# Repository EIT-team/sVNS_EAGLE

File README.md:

# sVNS_15chan_EAGLE

EAGLE project, schematic and layout files of the 15-channel selective Vagus Nerve stimulator. Eagle-based 4-layer PCB with SMD assembly were produced using PCBway services.

Note: 15 channels in the files names refer to a number of the output demultiplexer states.

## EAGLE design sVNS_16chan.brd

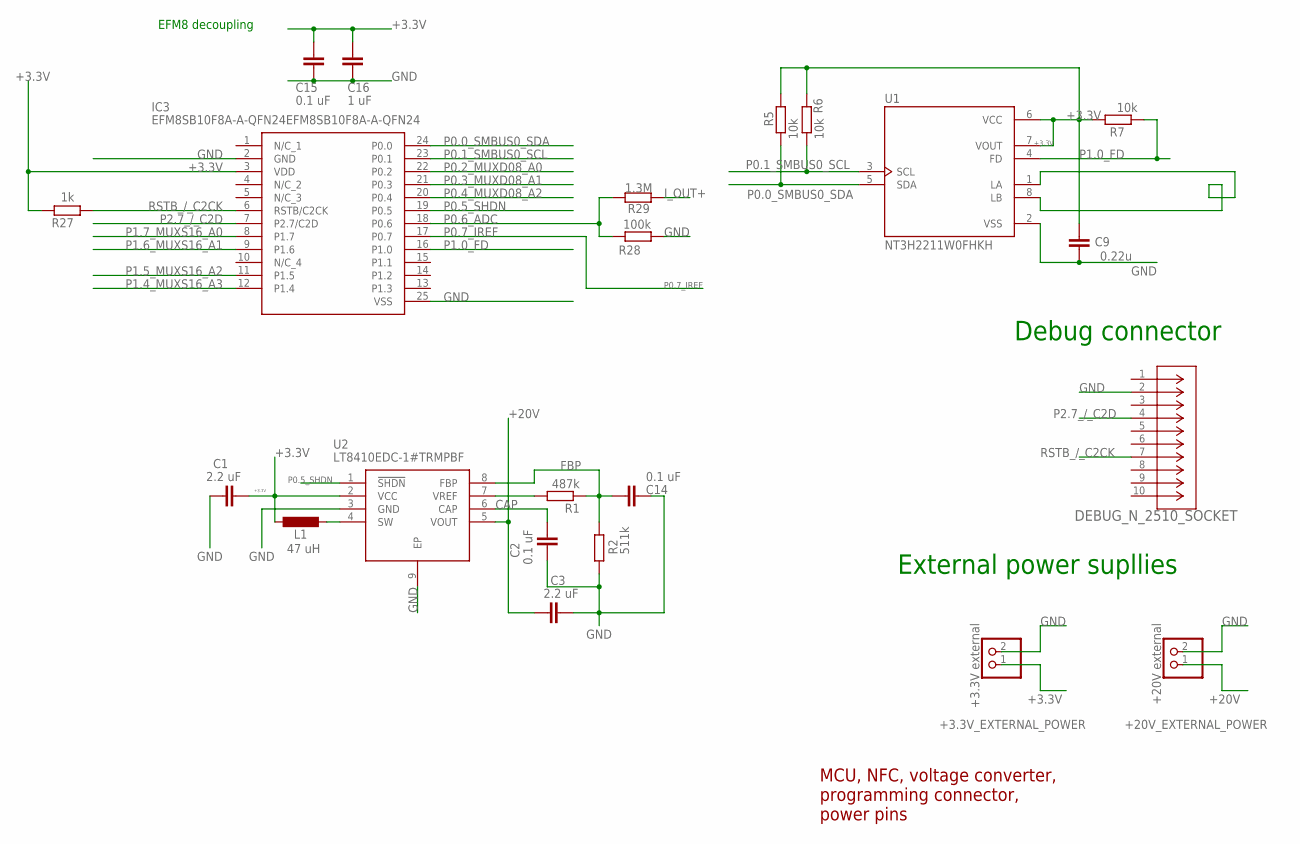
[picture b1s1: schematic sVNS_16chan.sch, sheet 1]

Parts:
+3.3V_EXTERNAL_POWER: +3.3V external; 1X02
+20V_EXTERNAL_POWER: +20V external; 1X02
C1, C3: 2.2 uF; C0603
C2, C14, C15: 0.1 uF; C0603
C9: 0.22u; C0603
C16: 1 uF; C0603
DEBUG_N_2510_SOCKET: N2510-6002RB; CONN_6002RB_3MM
IC3: EFM8SB10F8A-A-QFN24EFM8SB10F8A-A-QFN24; QFN50P400X400X80-25T245N
L1: 47 uH; 0603PS-473KRC
R1: 487k; R0603
R2: 511k; R0603
R5, R6, R7: 10k; R0603
R27: 1k; R0603
R28: 100k; R0603
R29: 1.3M; R0603
U1: NT3H2211W0FHKH; IC_NT3H2211W0FHKH
U2: LT8410EDC-1#TRMPBF; SON45P200X200X80-9N

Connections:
+3.3V: +3.3V_EXTERNAL_POWER.1, C1.2, C9.1, C15.2, C16.1, IC3.3 (VDD), L1.P$1 (1), R5.2, R6.2, R7.2, R27.2, U1.6 (VCC), U1.7 (VOUT), U2.2 (VCC); also elsewhere on the board
+20V: +20V_EXTERNAL_POWER.1, C3.1, U2.5 (VOUT); also elsewhere on the board
CAP: C2.2, U2.6 (CAP)
FBP: C14.2, R1.1, R2.2, U2.8 (FBP)
GND: +3.3V_EXTERNAL_POWER.2, +20V_EXTERNAL_POWER.2, C1.1, C2.1, C3.2, C9.2, C14.1, C15.1, C16.2, DEBUG_N_2510_SOCKET.2, IC3.2 (GND), IC3.25 (VSS), R2.1, R28.2, U1.2 (VSS), U2.3 (GND), U2.9 (EP); also elsewhere on the board
I_OUT+: R29.1; also elsewhere on the board
LA: U1.1 (LA), U1.8 (LB)
P0.0_SMBUS0_SDA: IC3.24 (P0.0), R5.1, U1.5 (SDA)
P0.1_SMBUS0_SCL: IC3.23 (P0.1), R6.1, U1.3 (SCL)
P0.2_MUXD08_A0: IC3.22 (P0.2); also elsewhere on the board
P0.3_MUXD08_A1: IC3.21 (P0.3); also elsewhere on the board
P0.4_MUXD08_A2: IC3.20 (P0.4); also elsewhere on the board
P0.5_SHDN: IC3.19 (P0.5), U2.1 (!SHDN); also elsewhere on the board
P0.6_ADC: IC3.18 (P0.6), R28.1, R29.2
P0.7_IREF: IC3.17 (P0.7); also elsewhere on the board
P1.0_FD: IC3.16 (P1.0), R7.1, U1.4 (FD)
P1.4_MUXS16_A3: IC3.12 (P1.4); also elsewhere on the board
P1.5_MUXS16_A2: IC3.11 (P1.5); also elsewhere on the board
P1.6_MUXS16_A1: IC3.9 (P1.6); also elsewhere on the board
P1.7_MUXS16_A0: IC3.8 (P1.7); also elsewhere on the board
P2.7_/_C2D: DEBUG_N_2510_SOCKET.4, IC3.7 (P2.7/C2D)
RSTB_/_C2CK: DEBUG_N_2510_SOCKET.7, IC3.6 (RSTB/C2CK), R27.1
SW: L1.P$2 (2), U2.4 (SW)
VREF: R1.2, U2.7 (VREF)

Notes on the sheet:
External power supllies
Debug connector
EFM8 decoupling
MCU, NFC, voltage converter, programming connector, power pins

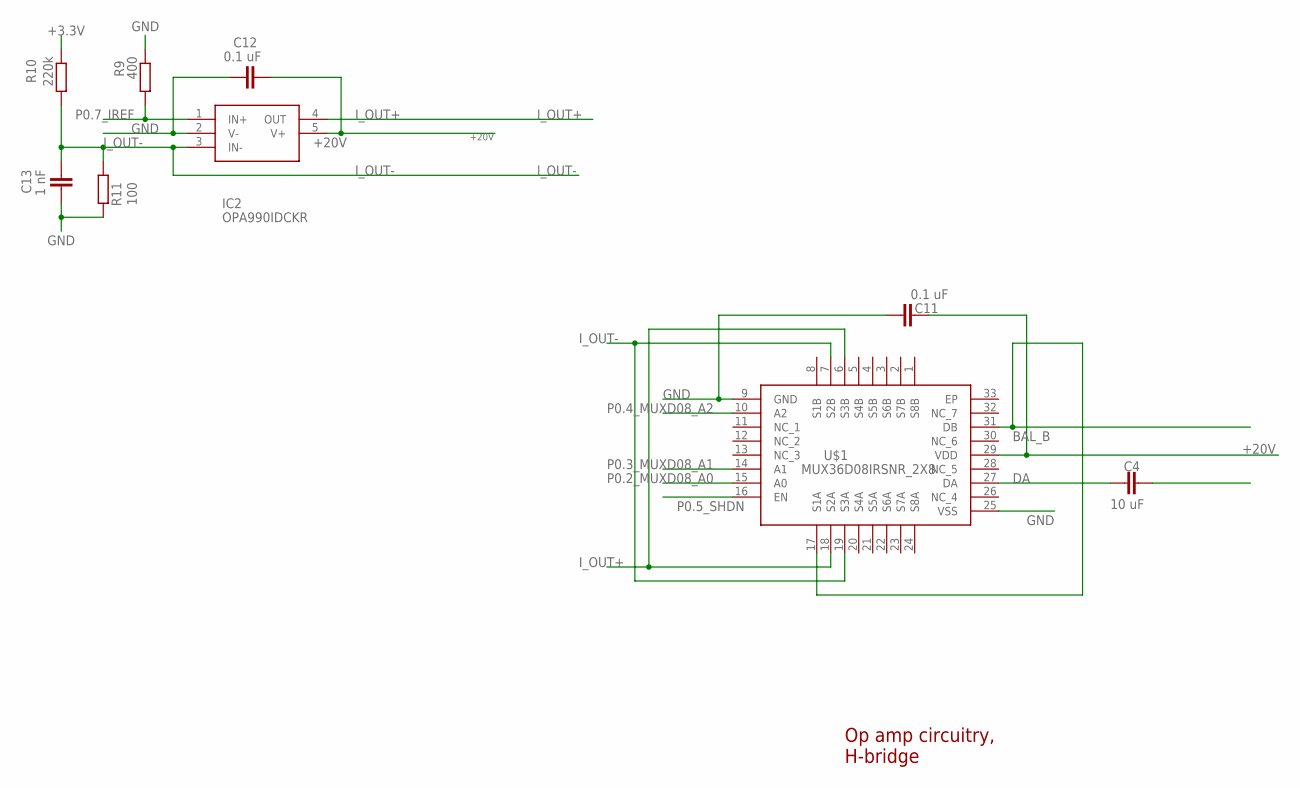
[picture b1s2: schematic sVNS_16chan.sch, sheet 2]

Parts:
C4: 10 uF; C0603
C11, C12: 0.1 uF; C0603
C13: 1 nF; C0603
IC2: OPA990IDCKR; SOT65P210X110-5N
R9: 400; R0603
R10: 220k; R0603
R11: 100; R0603
U$1: MUX36D08IRSNR_2X8; QFN40P400X400X80-33N_2X8

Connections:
+3.3V: R10.1; also elsewhere on the board
+20V: C11.2, C12.1, IC2.5 (V+), U$1.29 (VDD); also elsewhere on the board
BAL_A: C4.2; also elsewhere on the board
BAL_B: U$1.17 (S1A), U$1.31 (DB); also elsewhere on the board
DA: C4.1, U$1.27 (DA)
GND: C11.1, C12.2, C13.1, IC2.2 (V-), R9.1, R11.2, U$1.9 (GND), U$1.25 (VSS); also elsewhere on the board
I_OUT+: IC2.4 (OUT), U$1.6 (S3B), U$1.18 (S2A); also elsewhere on the board
I_OUT-: C13.2, IC2.3 (IN-), R10.2, R11.1, U$1.7 (S2B), U$1.19 (S3A)
P0.2_MUXD08_A0: U$1.15 (A0); also elsewhere on the board
P0.3_MUXD08_A1: U$1.14 (A1); also elsewhere on the board
P0.4_MUXD08_A2: U$1.10 (A2); also elsewhere on the board
P0.5_SHDN: U$1.16 (EN); also elsewhere on the board
P0.7_IREF: IC2.1 (IN+), R9.2; also elsewhere on the board

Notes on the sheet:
Op amp circuitry, H-bridge

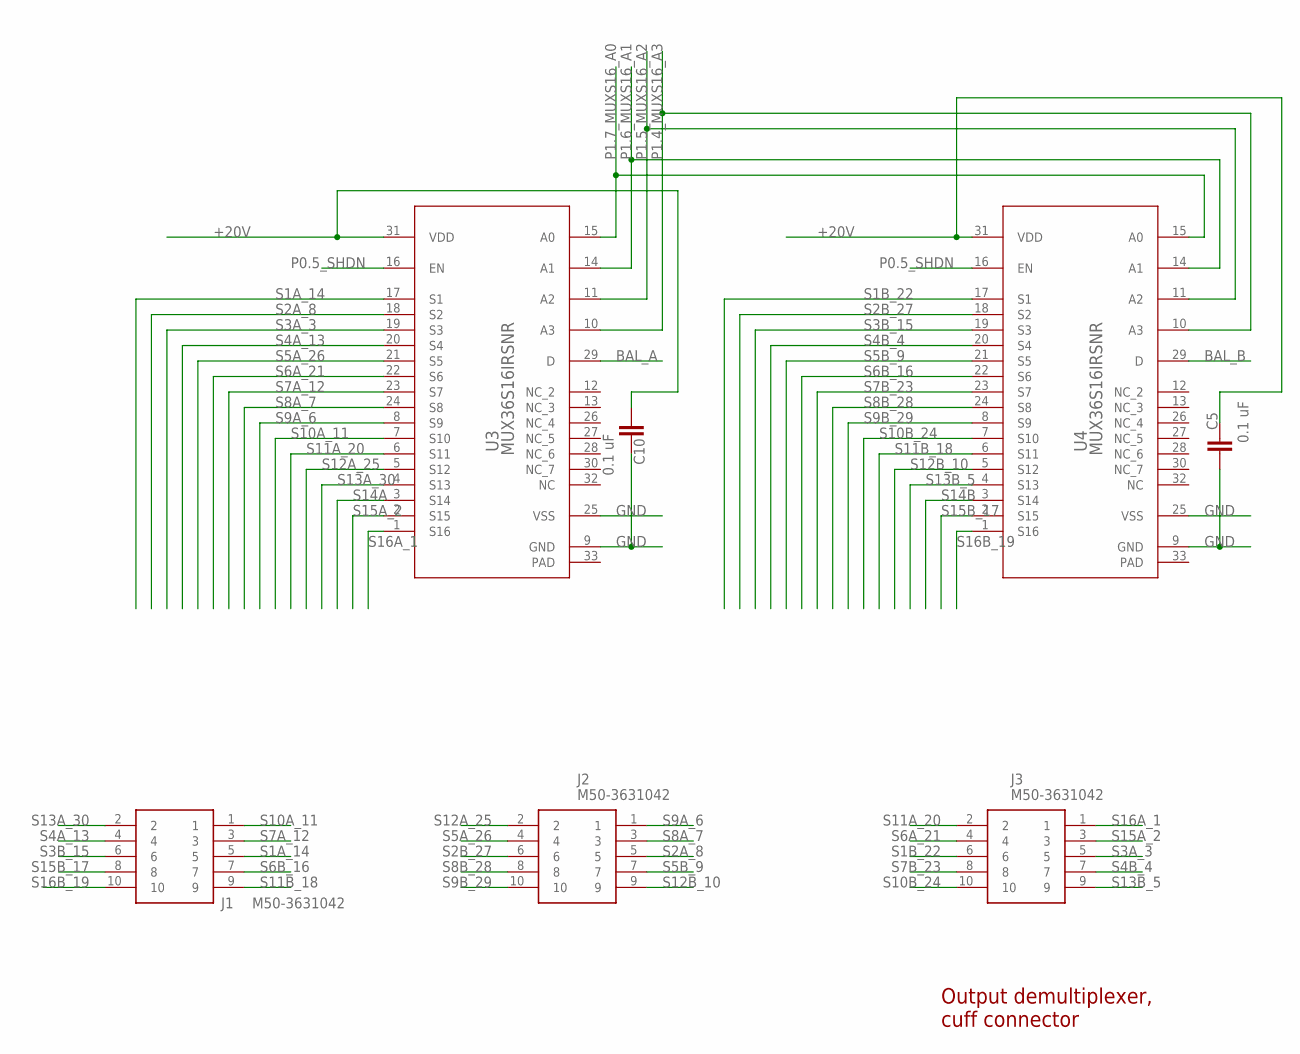
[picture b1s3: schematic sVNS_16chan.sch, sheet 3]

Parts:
C5, C10: 0.1 uF; C0603
J1, J2, J3: M50-3631042; M503631042
U3, U4: MUX36S16IRSNR; RSN0032B

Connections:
+20V: C5.2, C10.1, U3.31 (VDD), U4.31 (VDD); also elsewhere on the board
BAL_A: U3.29 (D); also elsewhere on the board
BAL_B: U4.29 (D); also elsewhere on the board
GND: C5.1, C10.2, U3.9 (GND), U3.25 (VSS), U4.9 (GND), U4.25 (VSS); also elsewhere on the board
P0.5_SHDN: U3.16 (EN), U4.16 (EN); also elsewhere on the board
P1.4_MUXS16_A3: U3.10 (A3), U4.10 (A3); also elsewhere on the board
P1.5_MUXS16_A2: U3.11 (A2), U4.11 (A2); also elsewhere on the board
P1.6_MUXS16_A1: U3.14 (A1), U4.14 (A1); also elsewhere on the board
P1.7_MUXS16_A0: U3.15 (A0), U4.15 (A0); also elsewhere on the board
S1A_14: J1.5, U3.17 (S1)
S1B_22: J3.6, U4.17 (S1)
S2A_8: J2.5, U3.18 (S2)
S2B_27: J2.6, U4.18 (S2)
S3A_3: J3.5, U3.19 (S3)
S3B_15: J1.6, U4.19 (S3)
S4A_13: J1.4, U3.20 (S4)
S4B_4: J3.7, U4.20 (S4)
S5A_26: J2.4, U3.21 (S5)
S5B_9: J2.7, U4.21 (S5)
S6A_21: J3.4, U3.22 (S6)
S6B_16: J1.7, U4.22 (S6)
S7A_12: J1.3, U3.23 (S7)
S7B_23: J3.8, U4.23 (S7)
S8A_7: J2.3, U3.24 (S8)
S8B_28: J2.8, U4.24 (S8)
S9A_6: J2.1, U3.8 (S9)
S9B_29: J2.10, U4.8 (S9)
S10A_11: J1.1, U3.7 (S10)
S10B_24: J3.10, U4.7 (S10)
S11A_20: J3.2, U3.6 (S11)
S11B_18: J1.9, U4.6 (S11)
S12A_25: J2.2, U3.5 (S12)
S12B_10: J2.9, U4.5 (S12)
S13A_30: J1.2, U3.4 (S13)
S13B_5: J3.9, U4.4 (S13)
S14A: U3.3 (S14)
S14B: U4.3 (S14)
S15A_2: J3.3, U3.2 (S15)
S15B_17: J1.8, U4.2 (S15)
S16A_1: J3.1, U3.1 (S16)
S16B_19: J1.10, U4.1 (S16)

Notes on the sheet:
Output demultiplexer, cuff connector

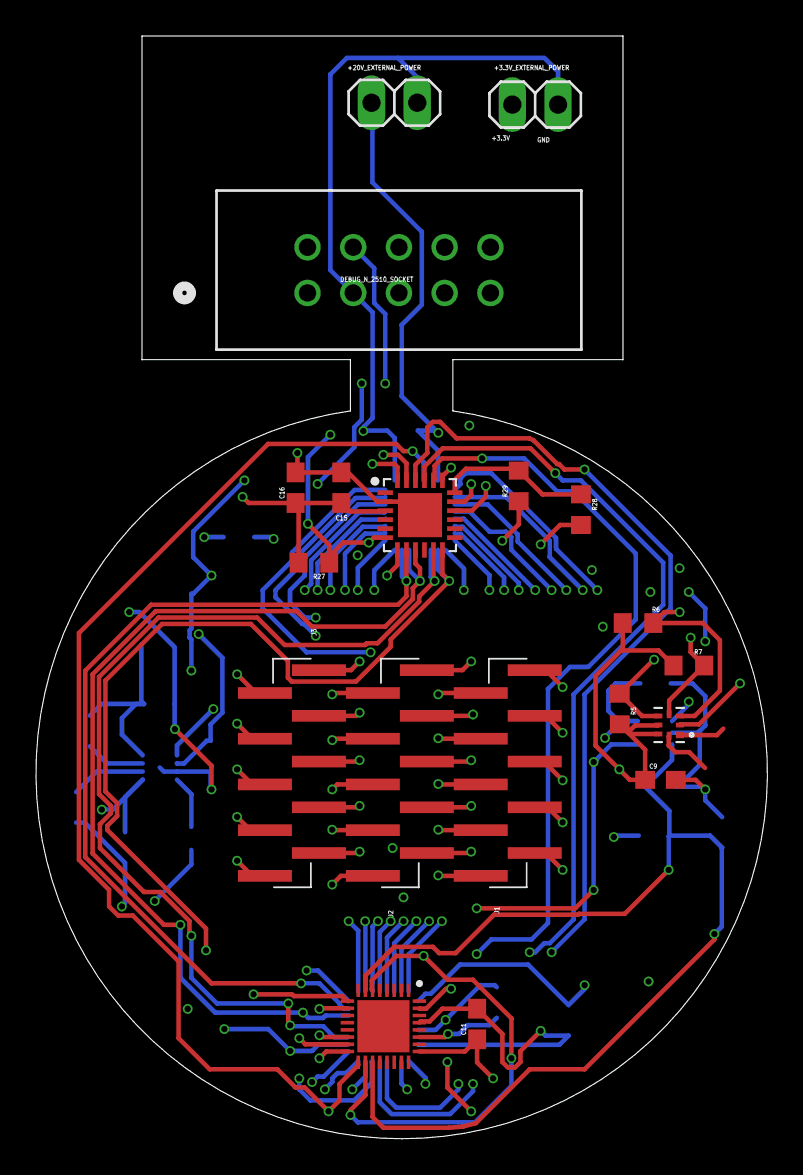
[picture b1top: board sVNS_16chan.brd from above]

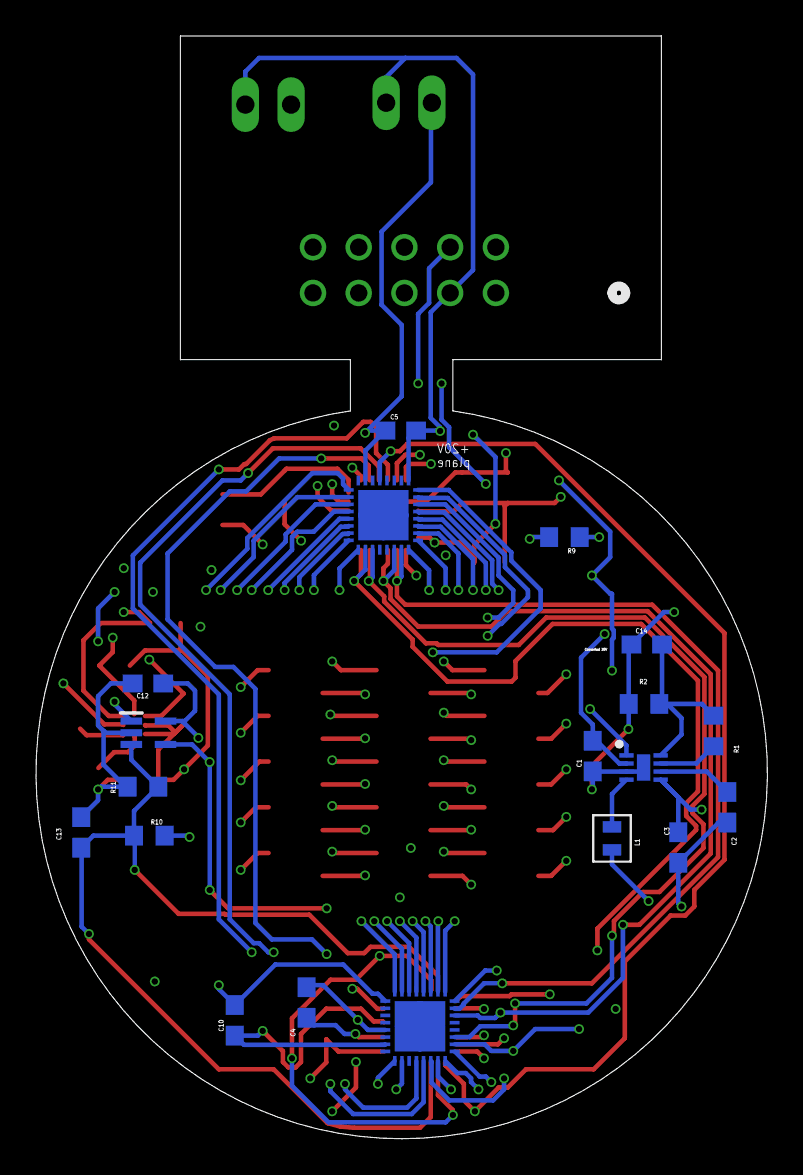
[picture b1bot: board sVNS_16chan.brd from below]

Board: 4 copper layers, 40.6 x 61.3 mm, 38 parts (19 on the bottom side), 58 nets.

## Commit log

2022-02-28 Initialized project for sVNS using 2x 16-channel multiplexers. Added sch draft.
2022-02-28 Added draft of gitignore
2022-03-02 Draft of 2x MUX36S16 for output and 1x MUX36D08 for H-bridge
2022-03-03 Schematic to submit to Enrico #1
2022-03-03 #1 submission to Enrico - fixed pin names
2022-03-05 Modified schematic as per Enricos suggestions
2022-03-05 Layout draft
2022-03-05 Setup/draft the top layer
2022-03-05 Modified sch (unknown change)
2022-03-06 Changed MUX36S16 part: removed annoying designator signs. Fixed generated 3.3V voltage check.
2022-03-06 Dual sided setup: components on both sides. Components grouped. No wiring yet.
2022-03-07 Decreased space between components. Changed the antenna connector. Ready for routing
2022-03-08 Experimentation and routing
2022-03-09 LT8410 and H-bridge relocated
2022-03-09 Replaced 0402 pads to 0603
2022-03-12 1) Updated .gitignore as per online recommendations 2) sch: added third sheet, separated output stage sch: deleted old pin sch: added surface mount male connectors and preliminary routed them 3) brd: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
2022-03-12 Experiment Richard 15:25
2022-03-12 LT8410 and op amp swapped. Optimised layout. Output pins moved to the top layer. Ready for MCU package change.
2022-03-12 Power planes added. Ready for power pin assignment, routing and EFM8 package change
2022-03-13 +3.3/+20V power pins assigned. Ready for control signal routing. Ready for MCU package change. Ready for MUXS16 rotaion
2022-03-13 Changed MCU package from CSP to QFN20. Ready to route signal traces. Ready for MUXS16 rotations
2022-03-14 Optimized component placement. Ready for signal routing. Ready for power/gnd vias.
2022-03-14 Routing half-done. Checkpoint 1
2022-03-14 Checkpoint 2
2022-03-14 Checkpoint 3. Output stage pin nets to be removed.
2022-03-14 Checkpoint 4. Output stage pin nets removed.
2022-03-14 Checkpoint 5. Closer to success?
2022-03-14 Component routing finished. ready for output stage routing.
2022-03-15 Decreased the board size. Removed dimensions
2022-03-15 Mapped output stage in the schematics
2022-03-15 Package change to QFN24
2022-03-15 Signal tracing. Checkpoint 1
2022-03-16 Signal tracing. Checkpoint 2
2022-03-18 Signal traces finished. Debug interface to be routed. Output stage to be mapped and routed
2022-03-18 Output stage mapped. Ready to be routed.
2022-03-19 Checkpoint 3. Output muxes moved, beginning to route the output
2022-03-19 Checkpoint 4. Optimized MUXes for output routing. Continue output routing
2022-03-19 Checkpoint 5. Stuck. Difficult wiring. Using autorouter
2022-03-19 Checkpoint 6. Success?
2022-03-20 Routed. Success
2022-03-26 Submitted and discussed latest QFN24 pcb version. Output stage mirrored. Only layer 1 and 16 used for routing
2022-03-26 Remapped output stage correctly. (It was mirrored before) Routed the debug connector and extended the board correctly. Ready for output stage routing.
2022-03-26 Routing output stage. Checkpoint 1
2022-03-26 Checkpoint 2. Used all available layers for the output stage routing. Almost done.
2022-03-27 Checkpoint 3. Success
2022-03-28 Increased track width. Layout/tracing finished.
2022-03-29 Prepared for PCBway assembly
2022-11-10 Synched current folder for the iteration 3 of the device.
2022-11-10 Checkpoint 1. Output capacitor changed to 10 uF, form factor 0603.
2022-11-12 Checkpoint 2. Minor changes and optimizations for the manufacturing. Output cap changed to 10 uF. Prepared for PCBway if this version considered to be manufactured.
2022-11-12 Checkpoint 2a. Minor addition to the keepout layer of the board. Not sure if mandatory.
2022-11-12 Checkpoint 3. Removed test pads on schematic. Ready for track retracing without the test pads. Existing wires preserved.
2022-11-12 Checkpoint 4. Major changes to the project: test pads removed. Tracks rerouted, initial component topology preserved.
2022-11-12 Checkpoint 4a. Tracks optimised. Original topology preserved. Width 23.67 mm. Length unchanged.
2022-11-14 Checkpoint 5. All unrouted traces finished. PCB optimised to 29.67 x 23.27.
2022-11-15 Checkpoint 6. Replaced all 20V associated 0402 components to 0603. Routed and optimised.
2022-11-15 Checkpoint 7. Replaced all components to 0603. Routed and optimised.
2022-11-15 Checkpoint 7a. Fixed the dimension label.
2022-11-17 Checkpoint 1. Initial circular PCB design. Trying out circular component placement.
2022-11-17 Checkpoint 2. Initial circular PCB routing attempts.
2022-11-18 Checkpoint 7b. Prepared for printing - removed some labels, optimized pcb to connector transition, rechecked with DRC.
2022-11-18 Checkpoint 7c. Minor changes after Gerber and support file generations.
2022-11-22 Checkpoint 3. Circular PCB routed except for the programming connector.
2022-11-23 Checkpoint 4. All routed and ready for check.
2022-11-24 Checkpoint 8. Noticed unreasonable 4 mil 20V power track. Changed it to 10 mils. Regenerated Gerbers.
2024-09-20 Checkpoint 5.1. Continue design of the circular PCB. Proceed to implementing the version with antenna as a copper track. 4 cm diameter, needs compactisation of peripheral tracks.
2025-03-05 V8.1. Added Bal_A label on the page 2 in the schematic, because only DA was shown before.

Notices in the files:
parts and their libraries:
COPYRIGHT: Copyright (C) 2021 Ultra Librarian. All rights reserved.
COPYRIGHT: Copyright (C) 2022 Ultra Librarian. All rights reserved.
